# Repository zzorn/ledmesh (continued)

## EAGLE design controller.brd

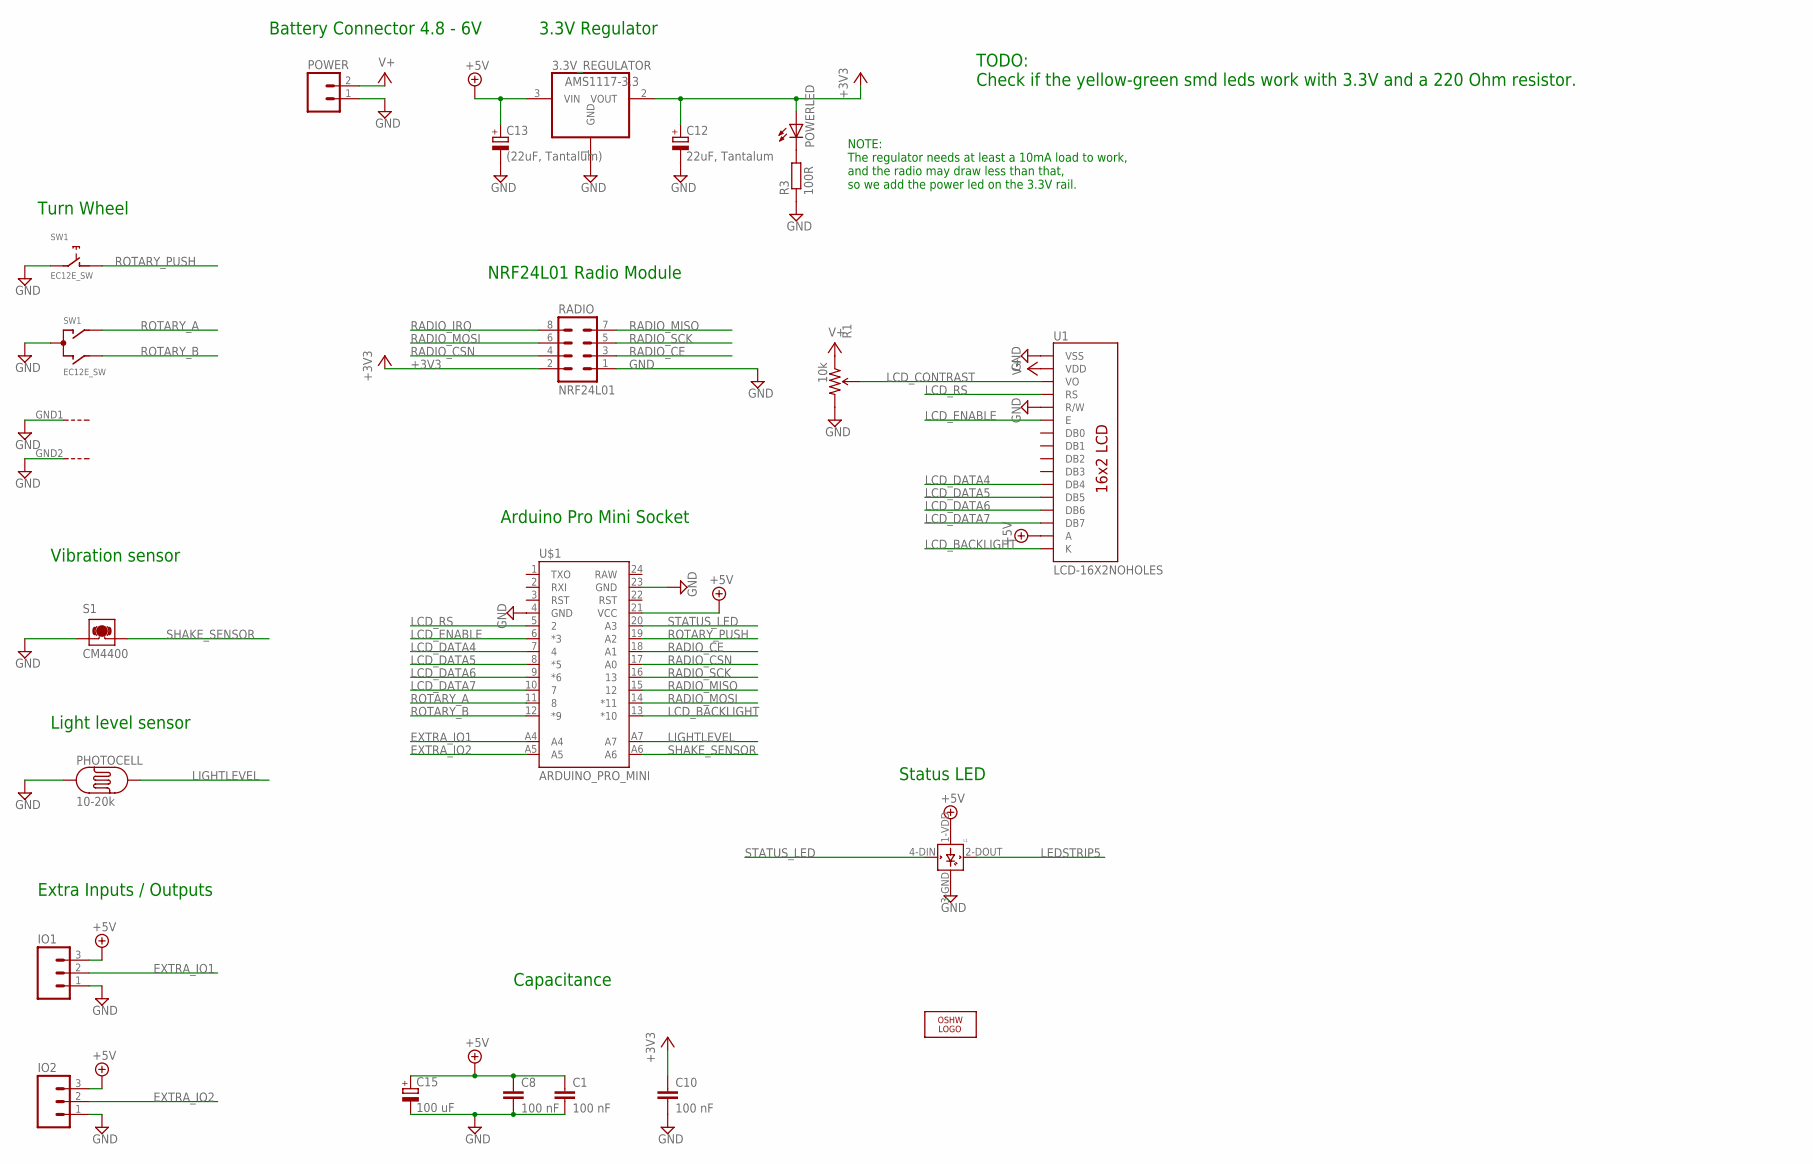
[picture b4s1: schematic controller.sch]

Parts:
3.3V_REGULATOR: AMS1117-3.3; SOT223
C1, C8, C10: 100 nF; C0805
C12: 22uF, Tantalum; SMC_A
C13: (22uF, Tantalum); SMC_A
C15: 100 uF; E2,5-6
IO1, IO2: M03PTH; 1X03
L1: WS2812B
LOGO3: LOGO-OSHW-8MILX0100-NT; OSHW_8X100_NOTEXT
PHOTOCELL: 10-20k; PHOTOCELL
POWER: M02LOCK_LONGPADS; 1X02_LOCK_LONGPADS
POWERLED: LEDSMT1206; 1206
R1: 10k; 3362U-2
R3: 100R; M0805
RADIO: NRF24L01; MA04-2
S1: CM4400
SW1: EC12E_SW; ALPS_EC12E_SW
U1: LCD-16X2NOHOLES; LCD-16X2_NOHOLES
U$1: ARDUINO_PRO_MINI

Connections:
+3V3: 3.3V_REGULATOR.2 (VOUT), C10.1, C12.+, POWERLED.A, RADIO.2
+5V: 3.3V_REGULATOR.3 (VIN), C1.1, C8.1, C13.+, C15.+, IO1.3, IO2.3, L1.1-VDD (VDD), U1.15 (A), U$1.21 (VCC)
EXTRA_IO1: IO1.2, U$1.A4
EXTRA_IO2: IO2.2, U$1.A5
GND: 3.3V_REGULATOR.1 (GND), C1.2, C8.2, C10.2, C12.-, C13.-, C15.-, IO1.1, IO2.1, L1.3-GND (GND), PHOTOCELL.1, POWER.1, R1.3 (CW), R3.1, RADIO.1, S1.1, SW1.C, SW1.E (2), SW1.GND1 (G), SW1.GND2 (G), U1.1 (VSS), U1.5 (R/W), U$1.4 (GND), U$1.23 (GND)
LCD_BACKLIGHT: U1.16 (K), U$1.13 (*10)
LCD_CONTRAST: R1.2 (WIPER), U1.3 (VO)
LCD_DATA4: U1.11 (DB4), U$1.7 (4)
LCD_DATA5: U1.12 (DB5), U$1.8 (*5)
LCD_DATA6: U1.13 (DB6), U$1.9 (*6)
LCD_DATA7: U1.14 (DB7), U$1.10 (7)
LCD_ENABLE: U1.6 (E), U$1.6 (*3)
LCD_RS: U1.4 (RS), U$1.5 (2)
LEDSTRIP5: L1.2-DOUT (DOUT)
LIGHTLEVEL: PHOTOCELL.2, U$1.A7
unnamed: POWERLED.C, R3.2
RADIO_CE: RADIO.3, U$1.18 (A1)
RADIO_CSN: RADIO.4, U$1.17 (A0)
RADIO_IRQ: RADIO.8
RADIO_MISO: RADIO.7, U$1.15 (12)
RADIO_MOSI: RADIO.6, U$1.14 (*11)
RADIO_SCK: RADIO.5, U$1.16 (13)
ROTARY_A: SW1.A, U$1.11 (8)
ROTARY_B: SW1.B, U$1.12 (*9)
ROTARY_PUSH: SW1.D (1), U$1.19 (A2)
SHAKE_SENSOR: S1.2, U$1.A6
STATUS_LED: L1.4-DIN (DIN), U$1.20 (A3)
V+: POWER.2, R1.1 (CCW), U1.2 (VDD)

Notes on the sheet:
Arduino Pro Mini Socket
Capacitance
Light level sensor
Extra Inputs / Outputs
Battery Connector 4.8 - 6V
NRF24L01 Radio Module
3.3V Regulator
NOTE: The regulator needs at least a 10mA load to work, and the radio may draw less than that, so we add the power led on the 3.3V rail.
TODO: Check if the yellow-green smd leds work with 3.3V and a 220 Ohm resistor.
Status LED
Vibration sensor
Turn Wheel

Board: 2 copper layers, 21 parts (11 on the bottom side), 26 nets, no tracks yet.

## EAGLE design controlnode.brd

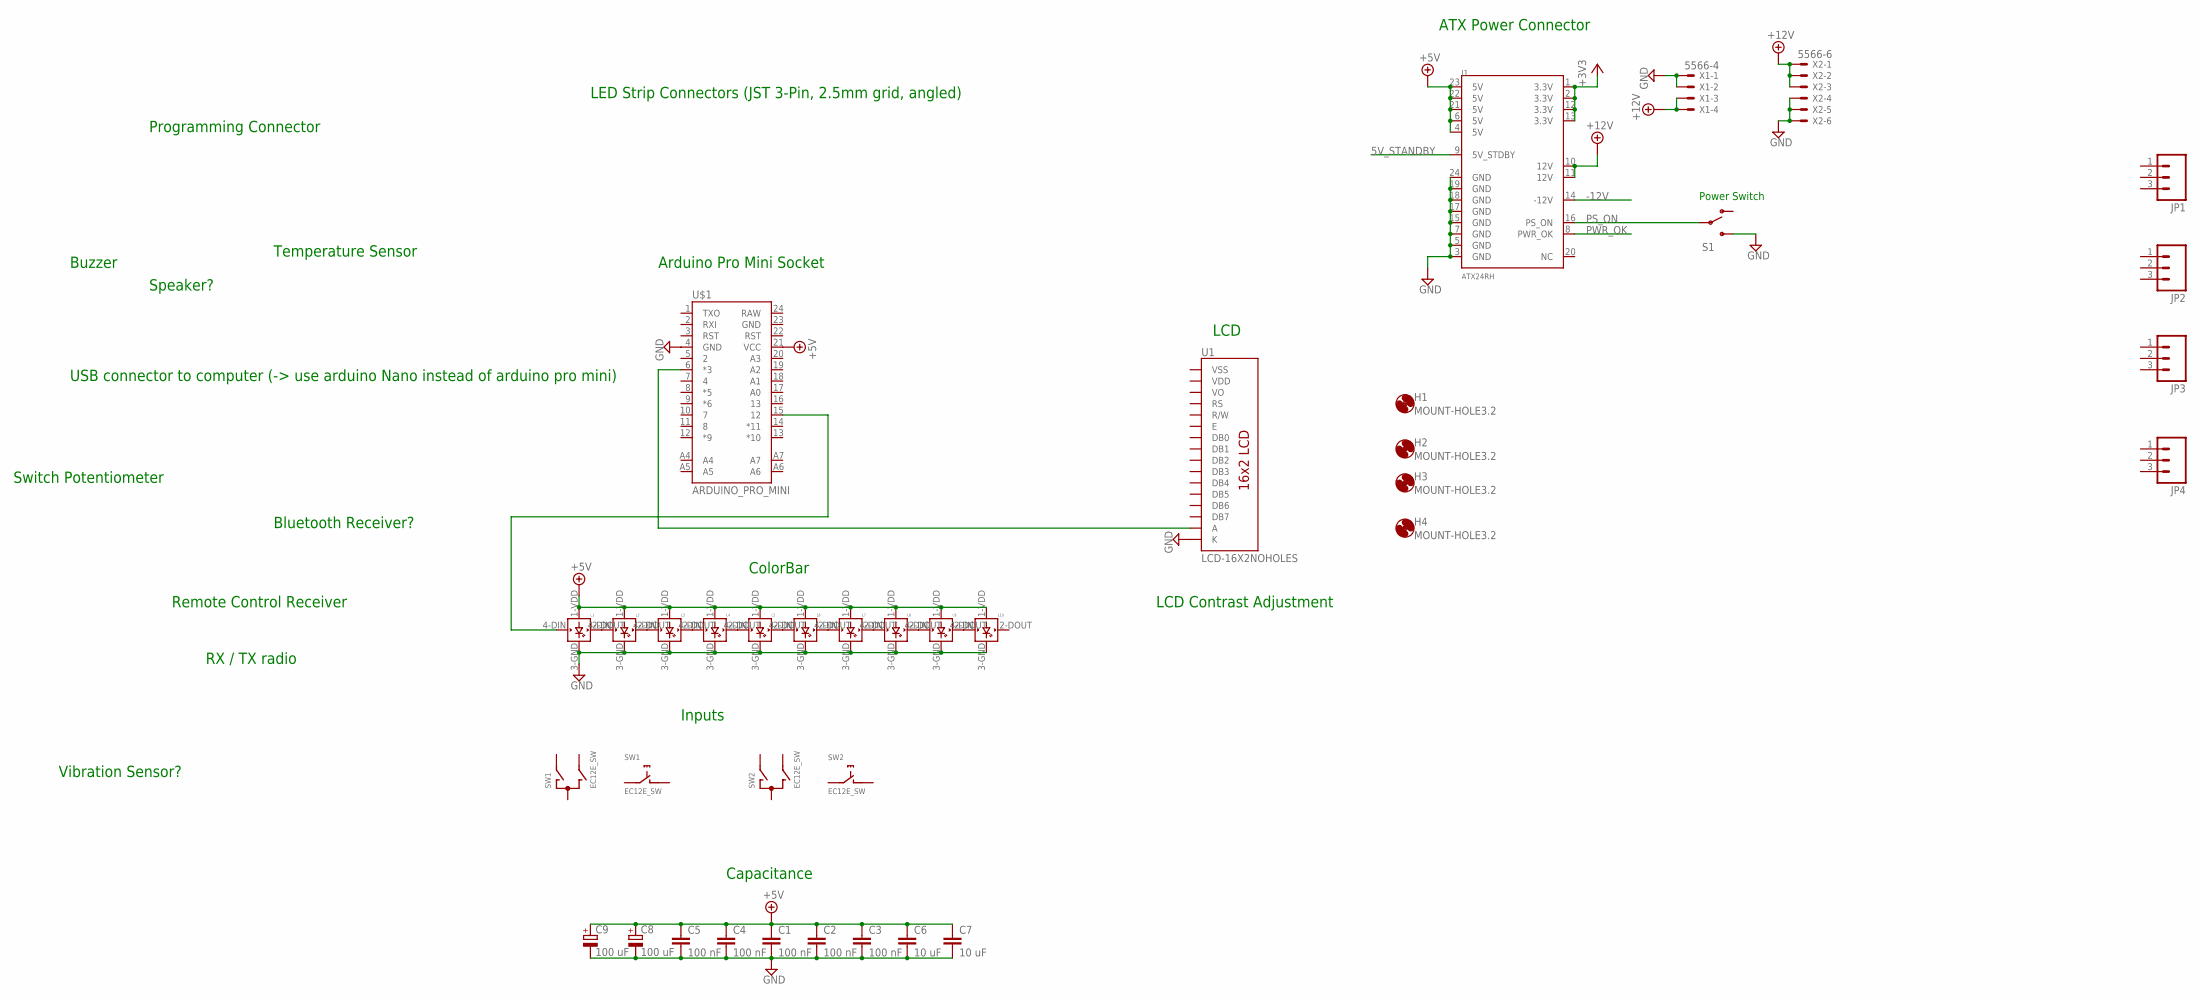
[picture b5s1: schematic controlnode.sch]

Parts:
C1, C2, C3, C4, C5: 100 nF; C0805
C6, C7: 10 uF; C1206
C8, C9: 100 uF; E3,5-10
H1, H2, H3, H4: MOUNT-HOLE3.2; 3,2
J1: ATX24RH; ATX24_RIGHT_ANGLE
JP1, JP2, JP3, JP4: M03-SCREW-5MM; SCREWTERMINAL-5MM-3
L1, L2, L3, L4, L5, L6, L7, L8, L9, L10: WS2812B
S1: SWITCH-SPSTPTH; SWITCH-SPDT
SW1, SW2: EC12E_SW; ALPS_EC12E_SW
U1: LCD-16X2NOHOLES; LCD-16X2_NOHOLES
U$1: ARDUINO_PRO_MINI
X1: 5566-4
X2: 5566-6

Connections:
5V_STANDBY: J1.9 (5V_STDBY)
+3V3: J1.1 (3.3V), J1.2 (3.3V), J1.12 (3.3V), J1.13 (3.3V)
+5V: C1.1, C2.1, C3.1, C4.1, C5.1, C6.1, C7.1, C8.+, C9.+, J1.4 (5V), J1.6 (5V), J1.21 (5V), J1.22 (5V), J1.23 (5V), L1.1-VDD (VDD), L2.1-VDD (VDD), L3.1-VDD (VDD), L4.1-VDD (VDD), L5.1-VDD (VDD), L6.1-VDD (VDD), L7.1-VDD (VDD), L8.1-VDD (VDD), L9.1-VDD (VDD), L10.1-VDD (VDD), U$1.21 (VCC)
+12V: J1.10 (12V), J1.11 (12V), X1.3, X1.4, X2.1, X2.2, X2.3
-12V: J1.14 (-12V)
GND: C1.2, C2.2, C3.2, C4.2, C5.2, C6.2, C7.2, C8.-, C9.-, J1.3 (GND), J1.5 (GND), J1.7 (GND), J1.15 (GND), J1.17 (GND), J1.18 (GND), J1.19 (GND), J1.24 (GND), L1.3-GND (GND), L2.3-GND (GND), L3.3-GND (GND), L4.3-GND (GND), L5.3-GND (GND), L6.3-GND (GND), L7.3-GND (GND), L8.3-GND (GND), L9.3-GND (GND), L10.3-GND (GND), S1.3 (S), U1.16 (K), U$1.4 (GND), X1.1, X1.2, X2.4, X2.5, X2.6
unnamed: L1.2-DOUT (DOUT), L2.4-DIN (DIN)
unnamed: L2.2-DOUT (DOUT), L3.4-DIN (DIN)
unnamed: L3.2-DOUT (DOUT), L4.4-DIN (DIN)
unnamed: L4.2-DOUT (DOUT), L5.4-DIN (DIN)
unnamed: L5.2-DOUT (DOUT), L6.4-DIN (DIN)
unnamed: L6.2-DOUT (DOUT), L7.4-DIN (DIN)
unnamed: L7.2-DOUT (DOUT), L8.4-DIN (DIN)
unnamed: L8.2-DOUT (DOUT), L9.4-DIN (DIN)
unnamed: L9.2-DOUT (DOUT), L10.4-DIN (DIN)
unnamed: L1.4-DIN (DIN), U$1.15 (12)
unnamed: U1.15 (A), U$1.6 (*3)
PS_ON: J1.16 (PS_ON), S1.2
PWR_OK: J1.8 (PWR_OK)
VDD: U1.2 (VDD)
VSS: U1.1 (VSS)

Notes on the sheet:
ATX Power Connector
Arduino Pro Mini Socket
LCD
Power Switch
Capacitance
ColorBar
Inputs
LED Strip Connectors (JST 3-Pin, 2.5mm grid, angled)
Programming Connector
LCD Contrast Adjustment
Remote Control Receiver
RX / TX radio
Buzzer
Speaker?
Switch Potentiometer
Vibration Sensor?
Temperature Sensor
Bluetooth Receiver?
USB connector to computer (-> use arduino Nano instead of arduino pro mini)

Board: 2 copper layers, 35 parts (14 on the bottom side), 16 nets, no tracks yet.

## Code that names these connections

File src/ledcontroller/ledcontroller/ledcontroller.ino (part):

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#define DEBUG_MODE true

// Pin assignments
#define LCD_RS_PIN        2
#define LCD_ENABLE_PIN    3
#define LCD_DATA4_PIN     4
#define LCD_DATA5_PIN     5
#define LCD_DATA6_PIN     6
#define LCD_DATA7_PIN     7
#define ROTARY_A_PIN      8 
#define ROTARY_B_PIN      9
#define LCD_BACKLIGHT_PIN 10
#define RADIO_MOSI_PIN    11
#define RADIO_MISO_PIN    12
#define RADIO_SCK_PIN     13    
#define RADIO_CSN_PIN     A0
#define RADIO_CE_PIN      A1 
#define ROTARY_PUSH_PIN   A2
#define STATUS_LED_PIN    A3
#define EXTRA_IO_1_PIN    A4
#define EXTRA_IO_2_PIN    A5
#define SHAKE_PIN         A6
#define LIGHTLEVEL_PIN    A7



// LCD library
LiquidCrystal lcd(LCD_RS_PIN, LCD_ENABLE_PIN, LCD_DATA4_PIN, LCD_DATA5_PIN, LCD_DATA6_PIN, LCD_DATA7_PIN);

// Singleton instance of the radio driver
RH_NRF24 driver(RADIO_CE_PIN, RADIO_CSN_PIN);

// Class to manage message delivery and receipt, using the driver declared above
RHDatagram manager(driver, SERVER_ADDRESS);
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
void setup() {
   /*
   pinMode(LCD_RS_PIN, OUTPUT);
   pinMode(LCD_ENABLE_PIN, OUTPUT);
   pinMode(LCD_DATA4_PIN, OUTPUT);
   pinMode(LCD_DATA5_PIN, OUTPUT);
   pinMode(LCD_DATA6_PIN, OUTPUT);
   pinMode(LCD_DATA7_PIN, OUTPUT);
   */
   pinMode(LCD_BACKLIGHT_PIN, OUTPUT);

   pinMode(STATUS_LED_PIN, OUTPUT);

   pinMode(EXTRA_IO_1_PIN, INPUT);
   pinMode(EXTRA_IO_2_PIN, INPUT);

   pinMode(ROTARY_A_PIN, INPUT);  
   pinMode(ROTARY_B_PIN, INPUT);  
   pinMode(ROTARY_PUSH_PIN, INPUT);

   pinMode(SHAKE_PIN, INPUT);
   pinMode(LIGHTLEVEL_PIN, INPUT);  


  Serial.begin(9600);
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  lcd.begin(16, 2);
  lcd.print("Light Controller");

  FastLED.addLeds<NEOPIXEL, STATUS_LED_PIN>(previewLeds, NUM_LEDS);

  // Defaults after init are 2.402 GHz (channel 2), 2Mbps, 0dBm
  if (!manager.init()) {
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    
  targetColor = randomColor(); 

  analogWrite(LCD_BACKLIGHT_PIN, 0);

 
}
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}

void previewColor(CRGB color) {
  // Send the color to the WS2812B led on pin STATUS_LED_PIN.
  previewLeds[0] = color; 
  FastLED.show(); 
}
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long averageAcceleration = 0;
long readEncoder() {
   long delta = 0; 
   int aPinStatus = digitalRead(ROTARY_A_PIN);
   if ((encoderPinALast == LOW) && (aPinStatus == HIGH)) {
     if (digitalRead(ROTARY_B_PIN) == LOW) {
       delta = -1;
     } else {
       delta = 1;
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  if (modeButtonCooldown_ms <= 0) {
    modeButtonCooldown_ms = 0;
    
    boolean pressedNow = (digitalRead(ROTARY_PUSH_PIN) == LOW);
  
    if (pressedNow != modeButtonPressed) {
      modeButtonCooldown_ms = modeButtonHysteresis_ms;
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
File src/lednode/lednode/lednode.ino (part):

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

// Pins
#define PIN_LEDSTRIP1 2
#define PIN_LEDSTRIP2 4
#define PIN_LEDSTRIP3 7
#define PIN_LEDSTRIP4 8

#define PIN_SPOTLIGHT1 3
#define PIN_SPOTLIGHT2 5
#define PIN_SPOTLIGHT3 6
#define PIN_SPOTLIGHT4 9
#define PIN_SPOTLIGHT5 10
#define PIN_SPOTLIGHT6 A3

#define PIN_RADIO_ENABLE A1
#define PIN_RADIO_CSN A0
#define PIN_RADIO_CLOCK 13
#define PIN_RADIO_MISO 12
#define PIN_RADIO_MOSI 11

#define PIN_SOUND_ANALOG A2
#define PIN_LIGHTLEVEL A7
#define PIN_PROXIMITY A6

#define PIN_EXTRAIO1 A4
#define PIN_EXTRAIO2 A5
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#define LEDSTRIP_COUNT 4

int ledstripPins[] = {
  PIN_LEDSTRIP1,
  PIN_LEDSTRIP2,
  PIN_LEDSTRIP3,
  PIN_LEDSTRIP4
};

#define SPOTLIGHT_COUNT 6

int spotlightPins[] = {
  PIN_SPOTLIGHT1,
  PIN_SPOTLIGHT2,
  PIN_SPOTLIGHT3,
  PIN_SPOTLIGHT4,
  PIN_SPOTLIGHT5,
  PIN_SPOTLIGHT6
};


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uint8_t thisNodeAddress = DEFAULT_NODE_ADDRESS;

// Singleton instance of the radio driver
RH_NRF24 driver(PIN_RADIO_ENABLE, PIN_RADIO_CSN);

// Class to manage message delivery and receipt, using the driver declared above
RHDatagram manager(driver, thisNodeAddress);
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
      // Kludge to manage pins that need to be passed in as constants
      switch(pin_) {
        case PIN_LEDSTRIP1: FastLED.addLeds<NEOPIXEL, PIN_LEDSTRIP1>(colors, ledCount); break;
        case PIN_LEDSTRIP2: FastLED.addLeds<NEOPIXEL, PIN_LEDSTRIP2>(colors, ledCount); break;
        case PIN_LEDSTRIP3: FastLED.addLeds<NEOPIXEL, PIN_LEDSTRIP3>(colors, ledCount); break;
        case PIN_LEDSTRIP4: FastLED.addLeds<NEOPIXEL, PIN_LEDSTRIP4>(colors, ledCount); break;
        default: printValue("Unsupported led strip pin ", pin_); break;
      }
    }
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  for (int i = 0; i < SPOTLIGHT_COUNT; i++) {
     pinMode(spotlightPins[i], OUTPUT);
  }
  pinMode(PIN_RADIO_ENABLE, OUTPUT);
  pinMode(PIN_RADIO_CSN, OUTPUT);
  pinMode(PIN_RADIO_CLOCK, OUTPUT);
  pinMode(PIN_RADIO_MOSI, OUTPUT);
  pinMode(PIN_RADIO_MISO, INPUT);

  pinMode(PIN_SOUND_ANALOG, INPUT);
  pinMode(PIN_LIGHTLEVEL, INPUT);
  pinMode(PIN_PROXIMITY, INPUT);

  pinMode(PIN_EXTRAIO1, INPUT);
  pinMode(PIN_EXTRAIO2, INPUT);
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  
  
  // DEBUG
  analogWrite(PIN_SPOTLIGHT1, 255);
  analogWrite(PIN_SPOTLIGHT2, 140);
  analogWrite(PIN_SPOTLIGHT3, 10);
  digitalWrite(PIN_SPOTLIGHT4, HIGH);
  digitalWrite(PIN_SPOTLIGHT5, HIGH);
  digitalWrite(PIN_SPOTLIGHT6, HIGH);
}


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
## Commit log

2010-12-21 Basic readme.
2010-12-21 Added used library to drive the LED PWM IC (TLC5940).
2014-09-13 Reused old project for new mesh networked led lightning project. Fleshed out general design plan in the readme document.
2014-09-13 Not using this IC in the new project.
2014-09-13 Gitignore.
2014-09-15 Lednode schema mostly done. Powernode still needs work.
2014-09-19 Finetned lednode schema, laid out components on lednode board, started routing.
2014-09-20 Layout and routing done, silkscreens mostly done.
2014-09-22 Final touches.
2014-09-22 Final cleanup and gerber generation.
2014-09-23 Started working on powernode. Separated controlnode into an own module.
2014-09-23 working on powernode.
2014-09-25 Working on powernone.
2014-09-26 Working on power / control node.
2014-09-27 Work on powernode.
2014-09-29 Working on powernode layout.
2014-10-01 Started working on version two of the led node, based on wireless communication.
2014-10-01 Working on new node version.
2014-10-02 Working on lednode v2.0
2014-10-03 Started working on ledcontroller software for the embedded arduinos.
2014-10-03 Tuning.
2014-10-10 Started working on (remote) controller.
2014-10-13 Tuning remote controller software.
2014-10-17 Simplified controller design, internal arduino pullup resistors can be used.
2014-10-18 Working on controller board. Simplified scamea a bit.
2014-10-29 Started working on smaller ledboard. Some updates to controll board.
2014-11-04 Finished lednode v 3.0.
2014-11-04 Added gerber files for lednode v 3.0.
2014-11-04 Updated readme.
2014-11-04 Removed generated gerber files. Moved eagle pcb design files to pcb/
2014-11-04 Removed old versions of the lednode and removed version numbers from the filenames.
2014-11-04 Removed some more version numbers from filenames.
2014-11-04 Removed old node designs.
2014-11-04 Removed unused file.
2014-11-04 Moved different pcbs to different directories.
2014-11-04 Simplified library dir name.
2014-11-04 Work on controller layout.
2014-11-06 Working on remote controller pcb. Added library with connectors and outlines of some of the used third party modules.
2014-11-30 Working on routing.
2014-12-03 Working on lednode software.
2014-12-20 Edits.
2014-12-21 Working on lednode.
